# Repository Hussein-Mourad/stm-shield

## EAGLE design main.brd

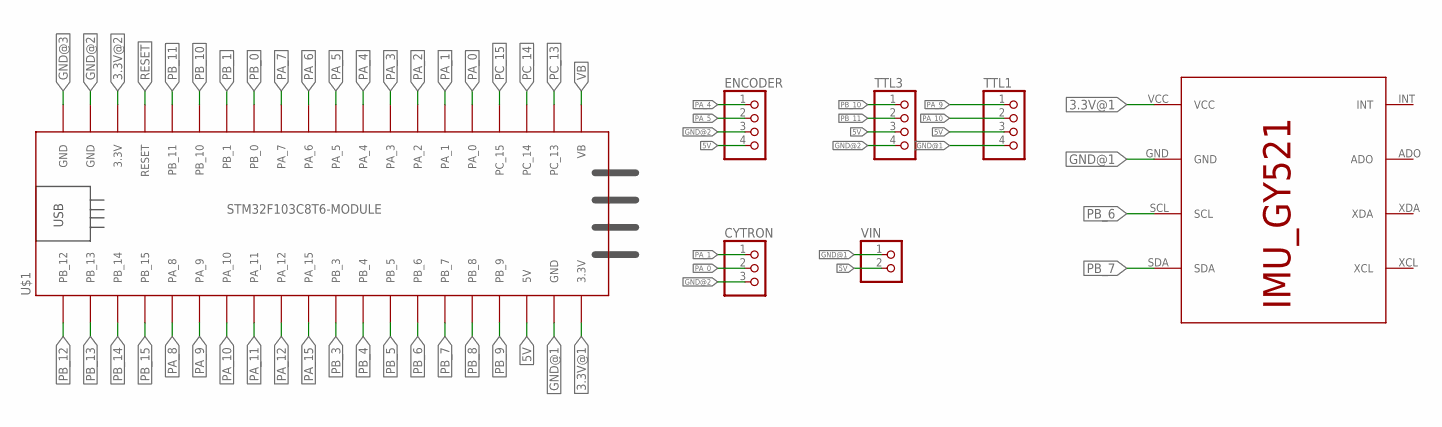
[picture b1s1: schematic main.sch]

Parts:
CYTRON: PINHD-3_DATA; 1X03_DATA
ENCODER: PINHD-4_DATA; 1X04_DATA
IMU: IMU_ROBOCON_GY521; IMU_GY521
TTL1, TTL3: PINHD-4_DATA; 1X04_DATA
U$1: STM32F103C8T6-MODULE
VIN: PINHD-2_DATA; 1X02_DATA

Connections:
3.3V@1: IMU.VCC, U$1.3.3V_1 (3.3V)
3.3V@2: U$1.3.3V_2 (3.3V)
5V: ENCODER.4, TTL1.3, TTL3.3, U$1.5V, VIN.2
GND@1: IMU.GND, TTL1.4, U$1.GND_1 (GND), VIN.1
GND@2: CYTRON.3, ENCODER.3, TTL3.4, U$1.GND_2 (GND)
GND@3: U$1.GND_3 (GND)
PA_0: CYTRON.2, U$1.PA_0
PA_1: CYTRON.1, U$1.PA_1
PA_2: U$1.PA_2
PA_3: U$1.PA_3
PA_4: ENCODER.1, U$1.PA_4
PA_5: ENCODER.2, U$1.PA_5
PA_6: U$1.PA_6
PA_7: U$1.PA_7
PA_8: U$1.PA_8
PA_9: TTL1.1, U$1.PA_9
PA_10: TTL1.2, U$1.PA_10
PA_11: U$1.PA_11
PA_12: U$1.PA_12
PA_15: U$1.PA_15
PB_0: U$1.PB_0
PB_1: U$1.PB_1
PB_3: U$1.PB_3
PB_4: U$1.PB_4
PB_5: U$1.PB_5
PB_6: IMU.SCL, U$1.PB_6
PB_7: IMU.SDA, U$1.PB_7
PB_8: U$1.PB_8
PB_9: U$1.PB_9
PB_10: TTL3.1, U$1.PB_10
PB_11: TTL3.2, U$1.PB_11
PB_12: U$1.PB_12
PB_13: U$1.PB_13
PB_14: U$1.PB_14
PB_15: U$1.PB_15
PC_13: U$1.PC_13
PC_14: U$1.PC_14
PC_15: U$1.PC_15
RESET: U$1.RESET
VB: U$1.VB

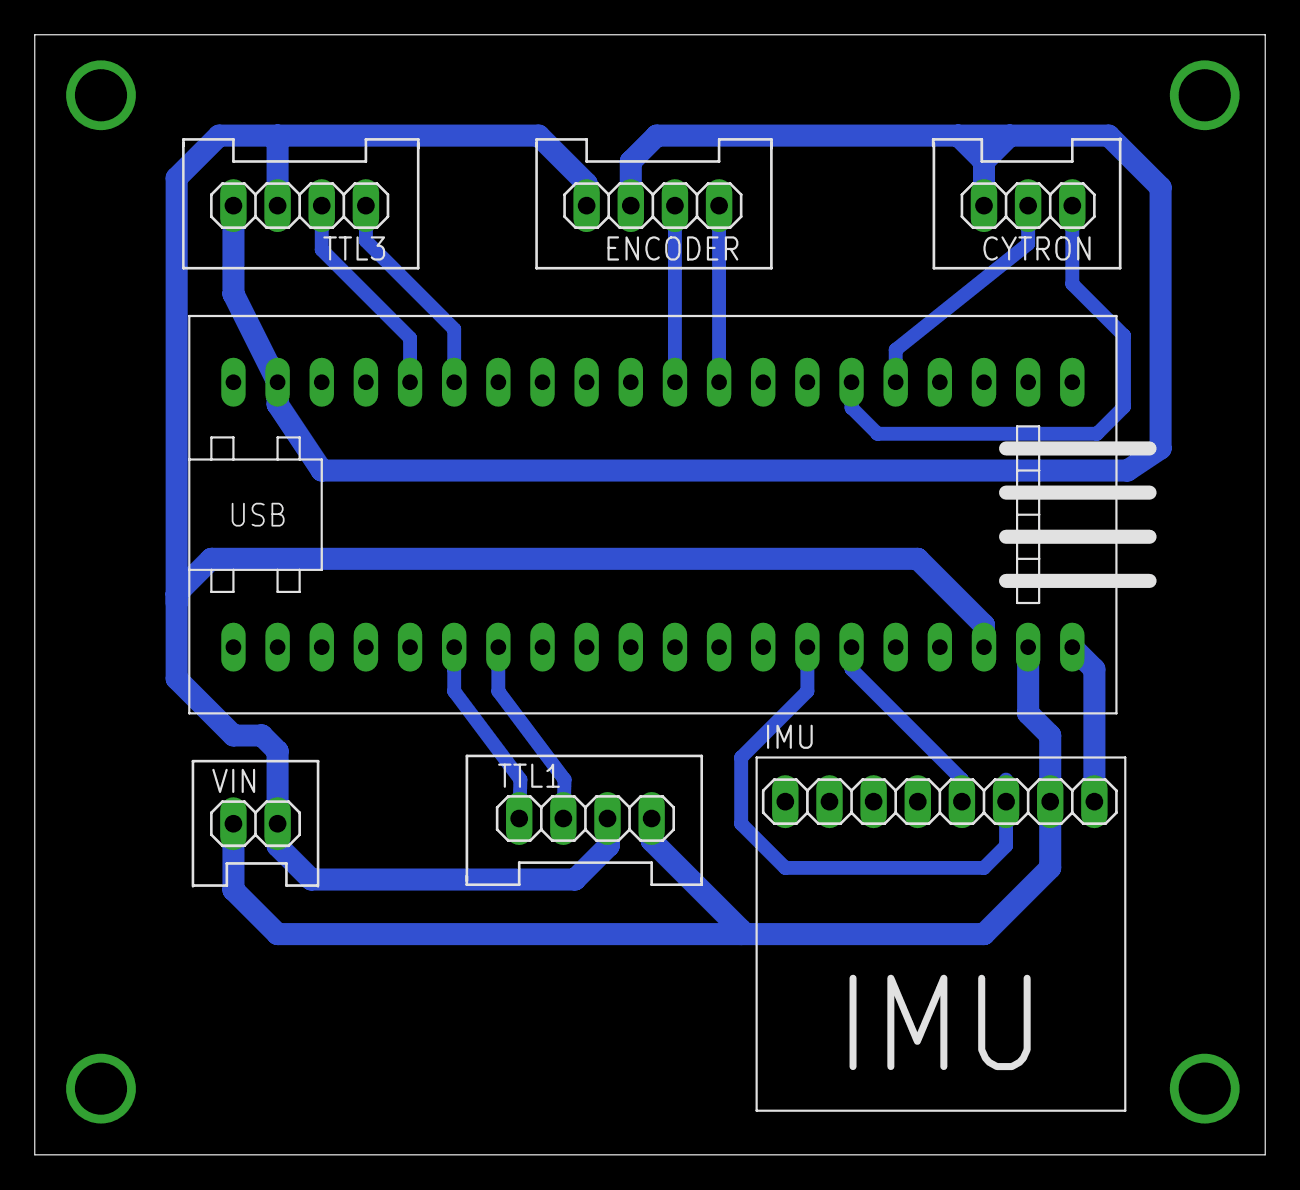
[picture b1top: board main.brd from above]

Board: 2 copper layers, 70.8 x 64.4 mm, 7 parts (0 on the bottom side), 14 nets.

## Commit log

2021-10-27 v1.0.0
2021-10-28 v1.1.0
2021-10-29 v1.2.0
